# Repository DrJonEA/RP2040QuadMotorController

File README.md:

# RP2040QuadMotorController
RP2040Zero and AT8236 Based Quad Motor Controller

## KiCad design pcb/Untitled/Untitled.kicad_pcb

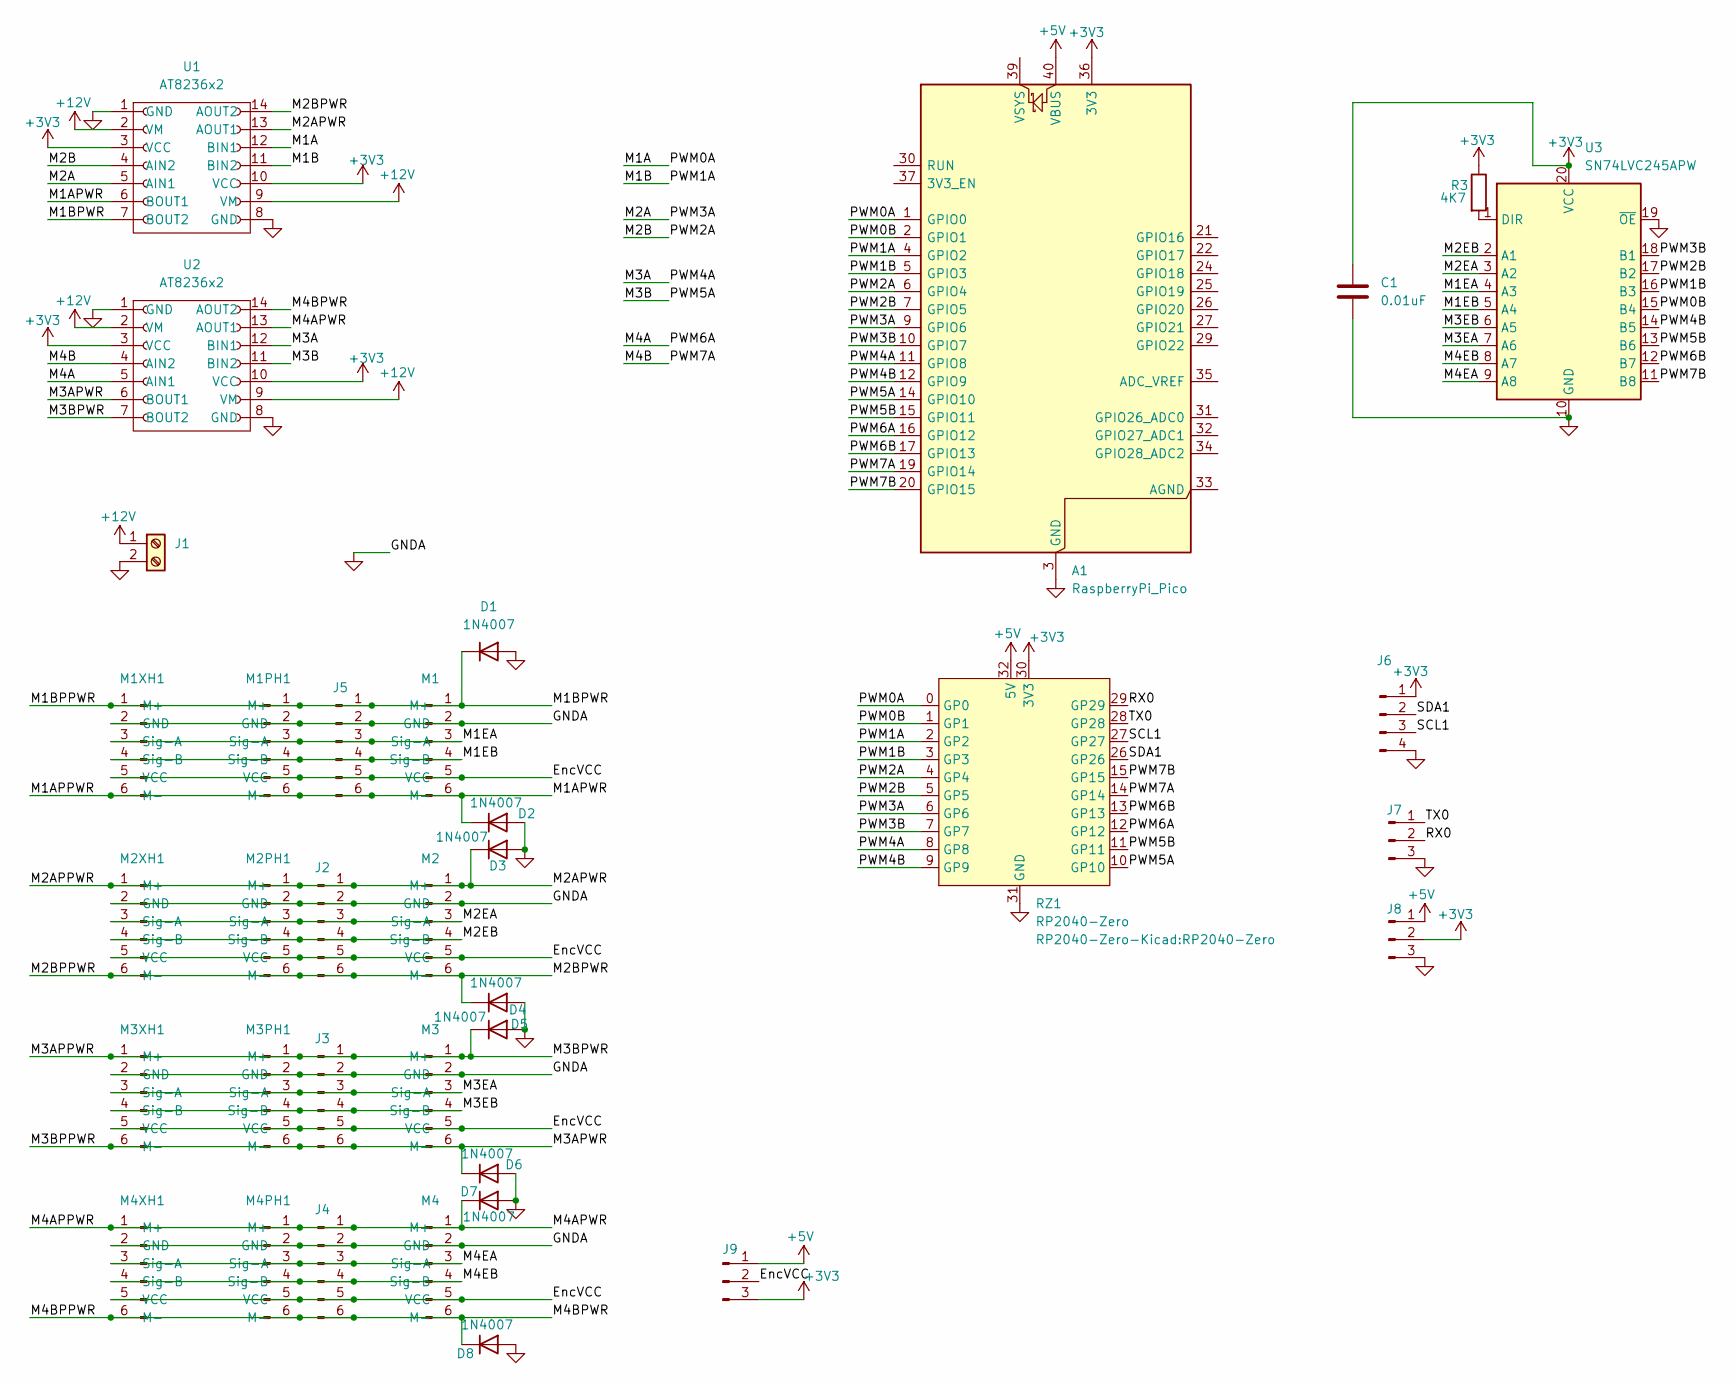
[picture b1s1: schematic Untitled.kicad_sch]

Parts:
A1: RaspberryPi_Pico; RaspberryPi_Pico_Common_Unspecified
C1: 0.01uF; C_Disc_D5.1mm_W3.2mm_P5.00mm
D1, D2, D3, D4, D5, D6, D7, D8: 1N4007; D_DO-41_SOD81_P10.16mm_Horizontal
J1: Screw_Terminal_01x02; ScrewTerm_Oiyagai_01x02_5mm
J2, J3, J4, J5: Conn_01x06_Pin; PinHeader_1x06_P2.54mm_Vertical
J6: Conn_01x04_Pin; PinHeader_1x04_P2.54mm_Vertical
J7, J8, J9: Conn_01x03_Pin; PinHeader_1x03_P2.54mm_Vertical
M1, M2, M3, M4: PinHeader_1x06_P2.54mm_Vertical
M1PH1, M2PH1, M3PH1, M4PH1: JST_PH_B6B-PH-K_1x06_P2.00mm_Vertical
M1XH1, M2XH1, M3XH1, M4XH1: JST_XH_B6B-XH-AM_1x06_P2.50mm_Vertical
R3: 4K7; R_Axial_DIN0207_L6.3mm_D2.5mm_P7.62mm_Horizontal
RZ1: RP2040-Zero
U1, U2: AT8236x2; AT236x2
U3: SN74LVC245APW; DIP-20_W7.62mm

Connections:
+3V3: A1.36 (3V3), C1.1, J6.1, J8.2, J9.3, R3.1, RZ1.30 (3V3), U1.3 (VCC), U1.10 (VCC), U2.3 (VCC), U2.10 (VCC), U3.20 (VCC)
+5V: A1.40 (VBUS), J8.1, J9.1, RZ1.32 (5V)
+12V: J1.1, U1.2 (VM), U1.9 (VM), U2.2 (VM), U2.9 (VM)
/EncVCC: J2.5, J3.5, J4.5, J5.5, J9.2, M1.5 (VCC), M1PH1.5 (VCC), M1XH1.5 (VCC), M2.5 (VCC), M2PH1.5 (VCC), M2XH1.5 (VCC), M3.5 (VCC), M3PH1.5 (VCC), M3XH1.5 (VCC), M4.5 (VCC), M4PH1.5 (VCC), M4XH1.5 (VCC)
/M1A: A1.1 (GPIO0), RZ1.0 (GP0), U1.12 (BIN1)
/M1APPWR: D2.1 (K), J5.6, M1.6 (M-), M1PH1.6 (M-), M1XH1.6 (M-), U1.6 (BOUT1)
/M1B: A1.4 (GPIO2), RZ1.2 (GP2), U1.11 (BIN2)
/M1BPPWR: D1.1 (K), J5.1, M1.1 (M+), M1PH1.1 (M+), M1XH1.1 (M+), U1.7 (BOUT2)
/M1EA: J5.3, M1.3 (Sig-A), M1PH1.3 (Sig-A), M1XH1.3 (Sig-A), U3.4 (A3)
/M1EB: J5.4, M1.4 (Sig-B), M1PH1.4 (Sig-B), M1XH1.4 (Sig-B), U3.5 (A4)
/M2A: A1.9 (GPIO6), RZ1.6 (GP6), U1.5 (AIN1)
/M2B: A1.6 (GPIO4), RZ1.4 (GP4), U1.4 (AIN2)
/M2EA: J2.3, M2.3 (Sig-A), M2PH1.3 (Sig-A), M2XH1.3 (Sig-A), U3.3 (A2)
/M2EB: J2.4, M2.4 (Sig-B), M2PH1.4 (Sig-B), M2XH1.4 (Sig-B), U3.2 (A1)
/M3A: A1.11 (GPIO8), RZ1.8 (GP8), U2.12 (BIN1)
/M3APPWR: D5.1 (K), J3.1, M3.1 (M+), M3PH1.1 (M+), M3XH1.1 (M+), U2.7 (BOUT2)
/M3APWR: D6.1 (K), J3.6, M3.6 (M-), M3PH1.6 (M-), M3XH1.6 (M-), U2.6 (BOUT1)
/M3B: A1.14 (GPIO10), RZ1.10 (GP10), U2.11 (BIN2)
/M3EA: J3.3, M3.3 (Sig-A), M3PH1.3 (Sig-A), M3XH1.3 (Sig-A), U3.7 (A6)
/M3EB: J3.4, M3.4 (Sig-B), M3PH1.4 (Sig-B), M3XH1.4 (Sig-B), U3.6 (A5)
/M4A: A1.16 (GPIO12), RZ1.12 (GP12), U2.5 (AIN1)
/M4APPWR: D7.1 (K), J4.1, M4.1 (M+), M4PH1.1 (M+), M4XH1.1 (M+), U2.13 (AOUT1)
/M4B: A1.19 (GPIO14), RZ1.14 (GP14), U2.4 (AIN2)
/M4BPPWR: D8.1 (K), J4.6, M4.6 (M-), M4PH1.6 (M-), M4XH1.6 (M-), U2.14 (AOUT2)
/M4EA: J4.3, M4.3 (Sig-A), M4PH1.3 (Sig-A), M4XH1.3 (Sig-A), U3.9 (A8)
/M4EB: J4.4, M4.4 (Sig-B), M4PH1.4 (Sig-B), M4XH1.4 (Sig-B), U3.8 (A7)
/PWM0B: A1.2 (GPIO1), RZ1.1 (GP1), U3.15 (B4)
/PWM1B: A1.5 (GPIO3), RZ1.3 (GP3), U3.16 (B3)
/PWM2B: A1.7 (GPIO5), RZ1.5 (GP5), U3.17 (B2)
/PWM3B: A1.10 (GPIO7), RZ1.7 (GP7), U3.18 (B1)
/PWM4B: A1.12 (GPIO9), RZ1.9 (GP9), U3.14 (B5)
/PWM5B: A1.15 (GPIO11), RZ1.11 (GP11), U3.13 (B6)
/PWM6B: A1.17 (GPIO13), RZ1.13 (GP13), U3.12 (B7)
/PWM7B: A1.20 (GPIO15), RZ1.15 (GP15), U3.11 (B8)
/RX0: J7.2, RZ1.29 (GP29)
/SCL1: J6.3, RZ1.27 (GP27)
/SDA1: J6.2, RZ1.26 (GP26)
/TX0: J7.1, RZ1.28 (GP28)
GND: A1.3 (GND), A1.8 (GND), A1.13 (GND), A1.18 (GND), A1.23 (GND), A1.28 (GND), A1.38 (GND), C1.2, D1.2 (A), D2.2 (A), D3.2 (A), D4.2 (A), D5.2 (A), D6.2 (A), D7.2 (A), D8.2 (A), J1.2, J2.2, J3.2, J4.2, J5.2, J6.4, J7.3, J8.3, M1.2 (GND), M1PH1.2 (GND), M1XH1.2 (GND), M2.2 (GND), M2PH1.2 (GND), M2XH1.2 (GND), M3.2 (GND), M3PH1.2 (GND), M3XH1.2 (GND), M4.2 (GND), M4PH1.2 (GND), M4XH1.2 (GND), RZ1.31 (GND), U1.1 (GND), U1.8 (GND), U2.1 (GND), U2.8 (GND), U3.10 (GND), U3.19 (~OE)
unnamed: R3.2, U3.1 (DIR)

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
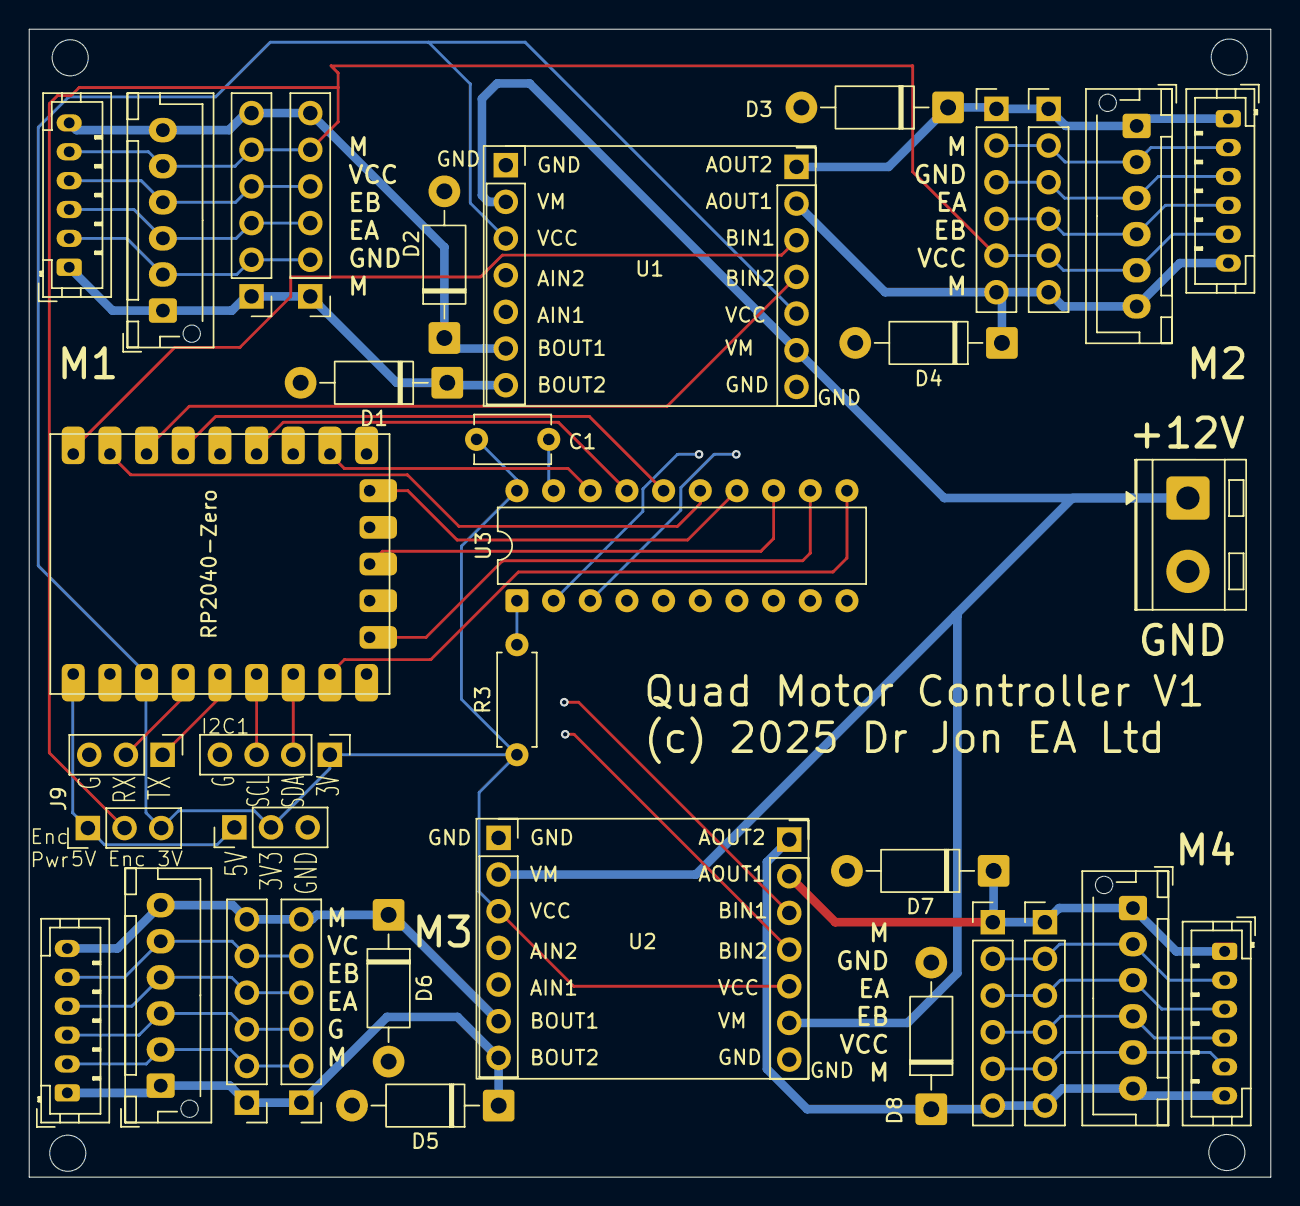
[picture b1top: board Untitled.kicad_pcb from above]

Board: 4 copper layers, 86.0 x 79.5 mm, 35 parts (0 on the bottom side), 42 nets.

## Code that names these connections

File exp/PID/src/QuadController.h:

/*
 * QuatController.h
 *
 *  Created on: 18 Dec 2025
 *      Author: jondurrant
 */

#ifndef EXP_SRC_QUATCONTROLLER_H_
#define EXP_SRC_QUATCONTROLLER_H_

#define UART0_TX 28
#define UART0_RX 29

#define SCL1 27
#define SDA1 26

//PWM Channels
#define PWM0A 0
#define PWM0B 1
#define PWM1A 2
#define PWM1B 3
#define PWM2A 4
#define PWM2B 5
#define PWM3A 6
#define PWM3B 7
#define PWM4A 8
#define PWM4B 9

#define PWM5A 10
#define PWM5B 11
#define PWM6A 12
#define PWM6B 13
#define PWM7A 14
#define PWM7B 15

//Motor Enconders
#define MTR1_ENC_A PWM1B
#define MTR1_ENC_B PWM0B
#define MTR2_ENC_A PWM2B
#define MTR2_ENC_B PWM3B
#define MTR3_ENC_A PWM5B
#define MTR3_ENC_B PWM4B
#define MTR4_ENC_A PWM6B
#define MTR4_ENC_B PWM7B

//Motor Power
#define MTR1_PWR_A PWM0A
#define MTR1_PWR_B PWM1A
#define MTR2_PWR_A PWM3A
#define MTR2_PWR_B PWM2A
#define MTR3_PWR_A PWM4A
#define MTR3_PWR_B PWM5A
#define MTR4_PWR_A PWM7A
#define MTR4_PWR_B PWM6A



#endif /* EXP_SRC_QUATCONTROLLER_H_ */

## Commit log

2025-12-18 Work in progress
2025-12-22 Added a Tachonometer board to test the project
2025-12-23 WIP PID
2025-12-24 Add fault detection and disabling
2025-12-24 Added Motor odemetry

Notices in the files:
pcb/Untitled/Untitled.kicad_pcb:
(c) 2025 Dr Jon EA Ltd
